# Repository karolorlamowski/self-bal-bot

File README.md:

# Self-balance-robot-project

Self balance robot project include CAD models of robot, PCB project and Python code.
You can control this robot by Xbox gamepad, also you can stream video of camera.
Robot has got ultrasonic sensors on it, but code is not prepared yet.

BOM:
* Pololu motor driver drv8835
* IMU MPU 6050
* Pololu motor encoders
* Raspberry Pi 3B+ or Raspberry Pi Zero W
* Pololu encoders
* Pololu 997 micro DC motors HP 100:1 
* Pi Camera

# Motor calibration

To calibrate your motors you need run script calibrate_motors.py and follow instructions listed on screen:

sudo python3 calibrate_motors.py

# IMU calibration

To calibrate your imu you need to put robot in horizontal position and run script calibrate_imu.py and follow instructions listed on screen:

sudo python3 calibrate_imu.py

# Xbox pad connection

To connect your xbox pad you need to use bluetoothctl:

1.install xbox pad drivers:

	sudo apt-get install xboxdrv
	
2. Disable Enhanced Re-Transmission Mode (ERTM):

	echo 'options bluetooth disable_ertm=Y' | sudo tee -a /etc/modprobe.d/bluetooth.conf
	
3. restart your Raspberry:

	sudo reboot now
	
4. Run bluetooth tools:

	sudo bluetoothctl
	
5. Now you need to search and connect to your pad, also you can trust yours device to connect automatically after each gamepad power on:

	agent on
	
	default-agent
	
	scan on
	
	connect GAMEPAD_MAC_ADDRESS
	
	trust GAMEPAD_MAC_ADDRESS

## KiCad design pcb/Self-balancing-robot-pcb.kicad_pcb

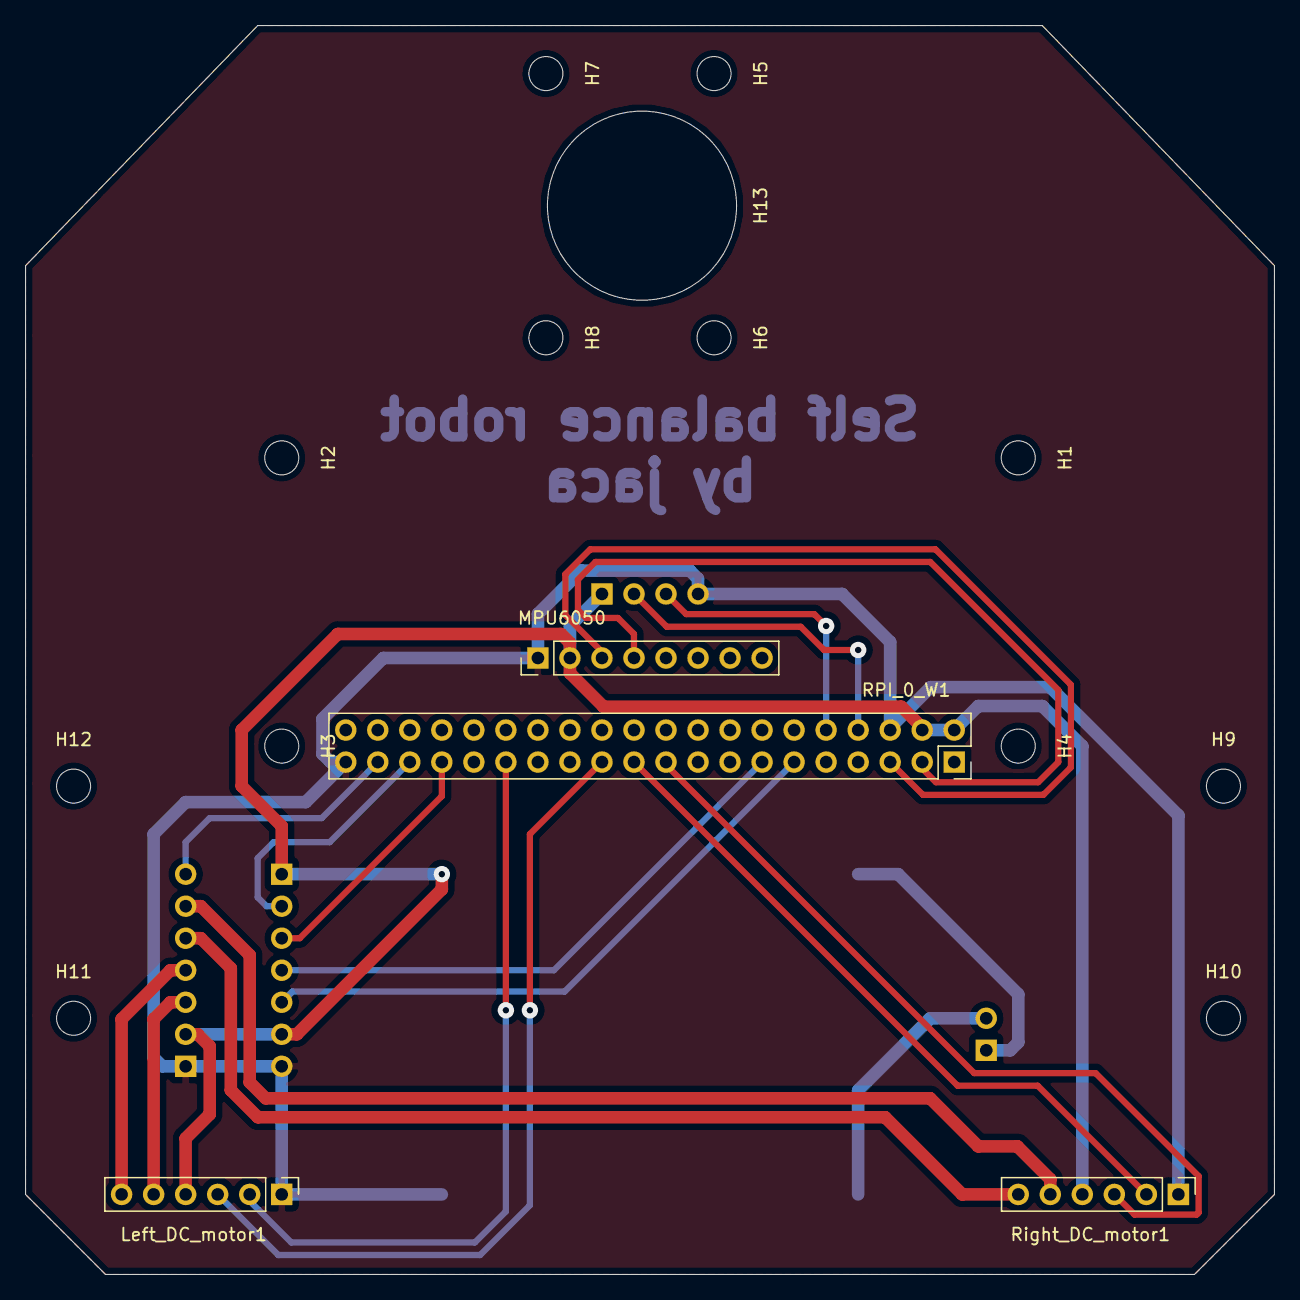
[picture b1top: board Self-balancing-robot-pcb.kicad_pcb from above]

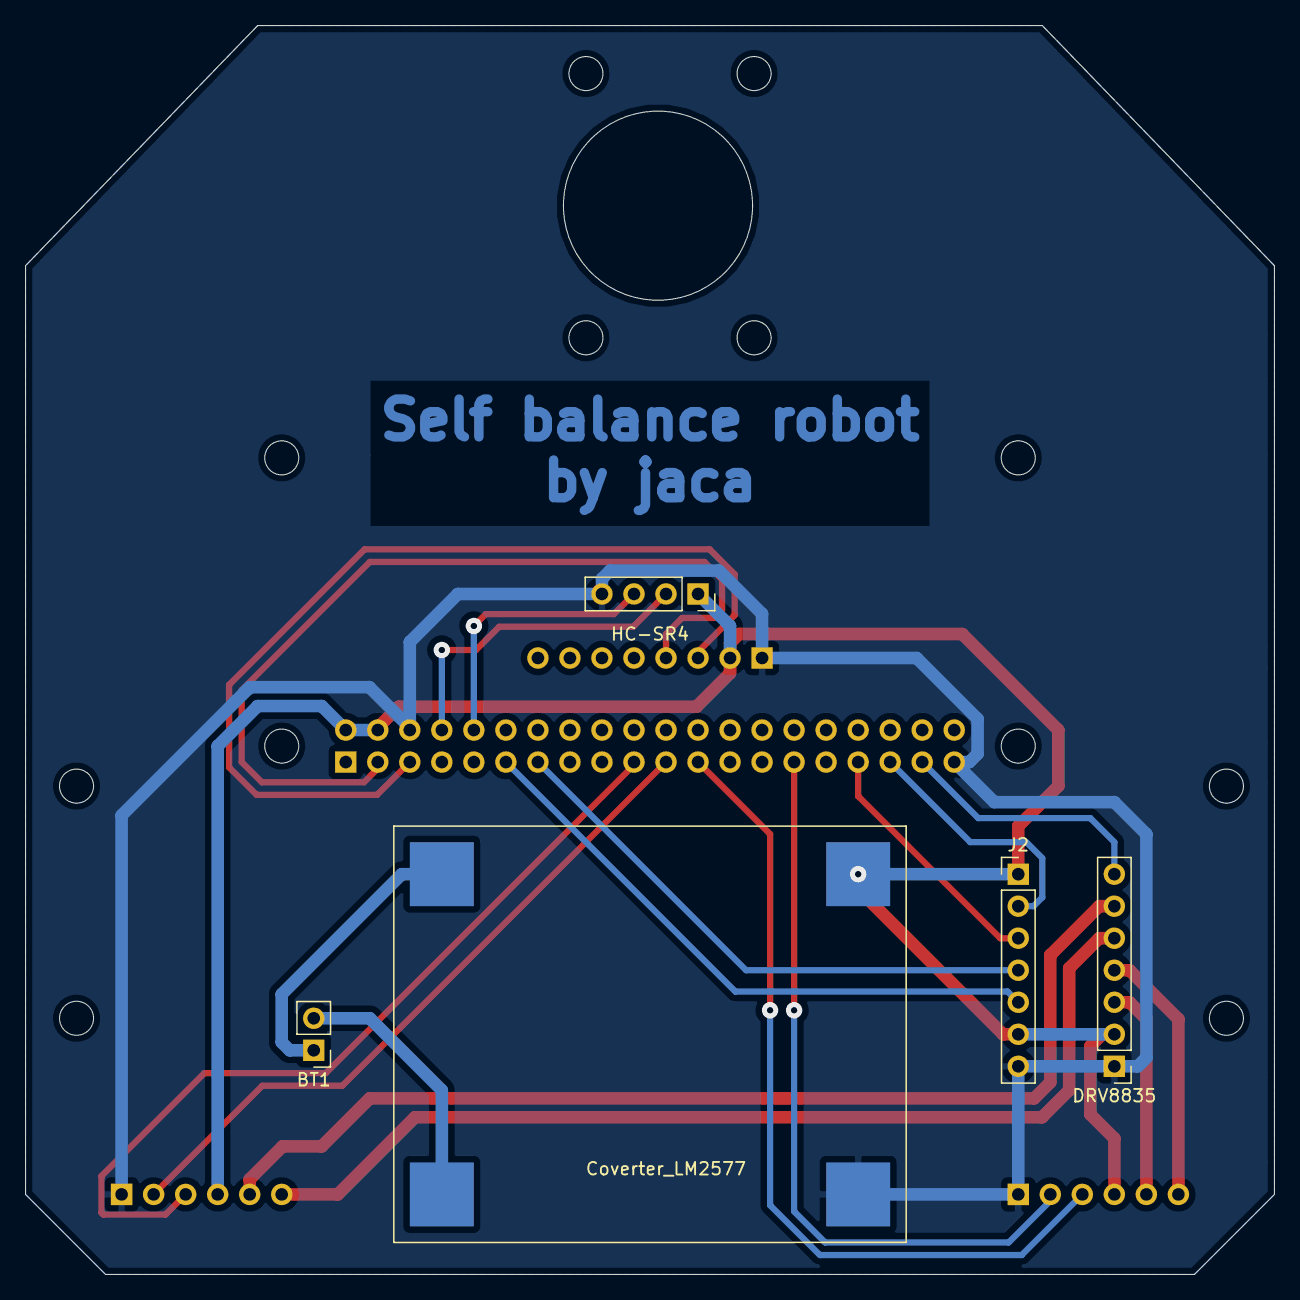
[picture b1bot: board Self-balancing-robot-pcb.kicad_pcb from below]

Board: 2 copper layers, 99.1 x 99.1 mm, 22 parts (5 on the bottom side), 21 nets.

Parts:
BT1: Battery_Cell; PinHeader_1x02_P2.54mm_Vertical
Coverter_LM2577: Step-up_converter; Step-up_converter_40x31
DRV8835: Conn_01x07; PinHeader_1x07_P2.54mm_Vertical
H1, H2, H3, H4, H5, H6, H7, H8, H9, H10, H11, H12: MountingHole; MountingHole_2.7mm_M2.5
H13: MountingHole; MountingHole_8.4mm_M8
HC-SR4: Conn_01x04_Female; PinSocket_1x04_P2.54mm_Vertical
J2: Conn_01x07; PinHeader_1x07_P2.54mm_Vertical
Left_DC_motor1: Conn_01x06_Female; PinHeader_1x06_P2.54mm_Vertical
MPU6050: Conn_01x08_Female; PinHeader_1x08_P2.54mm_Vertical
RPI_0_W1: Conn_02x20_Odd_Even; PinSocket_2x20_P2.54mm_Vertical
Right_DC_motor1: Conn_01x06_Female; PinHeader_1x06_P2.54mm_Vertical

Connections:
+5V: Coverter_LM2577.4, DRV8835.2, HC-SR4.1, J2.1, J2.6, Left_DC_motor1.4, MPU6050.2, RPI_0_W1.2, RPI_0_W1.4, Right_DC_motor1.4
ECHO: HC-SR4.3, RPI_0_W1.10
GND: Coverter_LM2577.3, DRV8835.1, HC-SR4.4, J2.7, Left_DC_motor1.1, MPU6050.1, RPI_0_W1.6, RPI_0_W1.39, Right_DC_motor1.1
IN1_PH_A: J2.2, RPI_0_W1.35
IN1_PH_B: J2.4, RPI_0_W1.13
IN2_EN_A: J2.3, RPI_0_W1.33
IN2_EN_B: J2.5, RPI_0_W1.11
L_M1: DRV8835.4, Left_DC_motor1.6
L_M2: DRV8835.3, Left_DC_motor1.5
L_OUT_A: Left_DC_motor1.3, RPI_0_W1.23
L_OUT_B: Left_DC_motor1.2, RPI_0_W1.29
MODE: DRV8835.7, RPI_0_W1.37
unnamed: BT1.1, Coverter_LM2577.1
unnamed: BT1.2, Coverter_LM2577.2
R_M1: DRV8835.5, Right_DC_motor1.6
R_M2: DRV8835.6, Right_DC_motor1.5
R_OUT_A: RPI_0_W1.19, Right_DC_motor1.3
R_OUT_B: RPI_0_W1.21, Right_DC_motor1.2
SCL: MPU6050.3, RPI_0_W1.5
SDA: MPU6050.4, RPI_0_W1.3
TRIG: HC-SR4.2, RPI_0_W1.8

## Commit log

2021-01-11 Init commit
